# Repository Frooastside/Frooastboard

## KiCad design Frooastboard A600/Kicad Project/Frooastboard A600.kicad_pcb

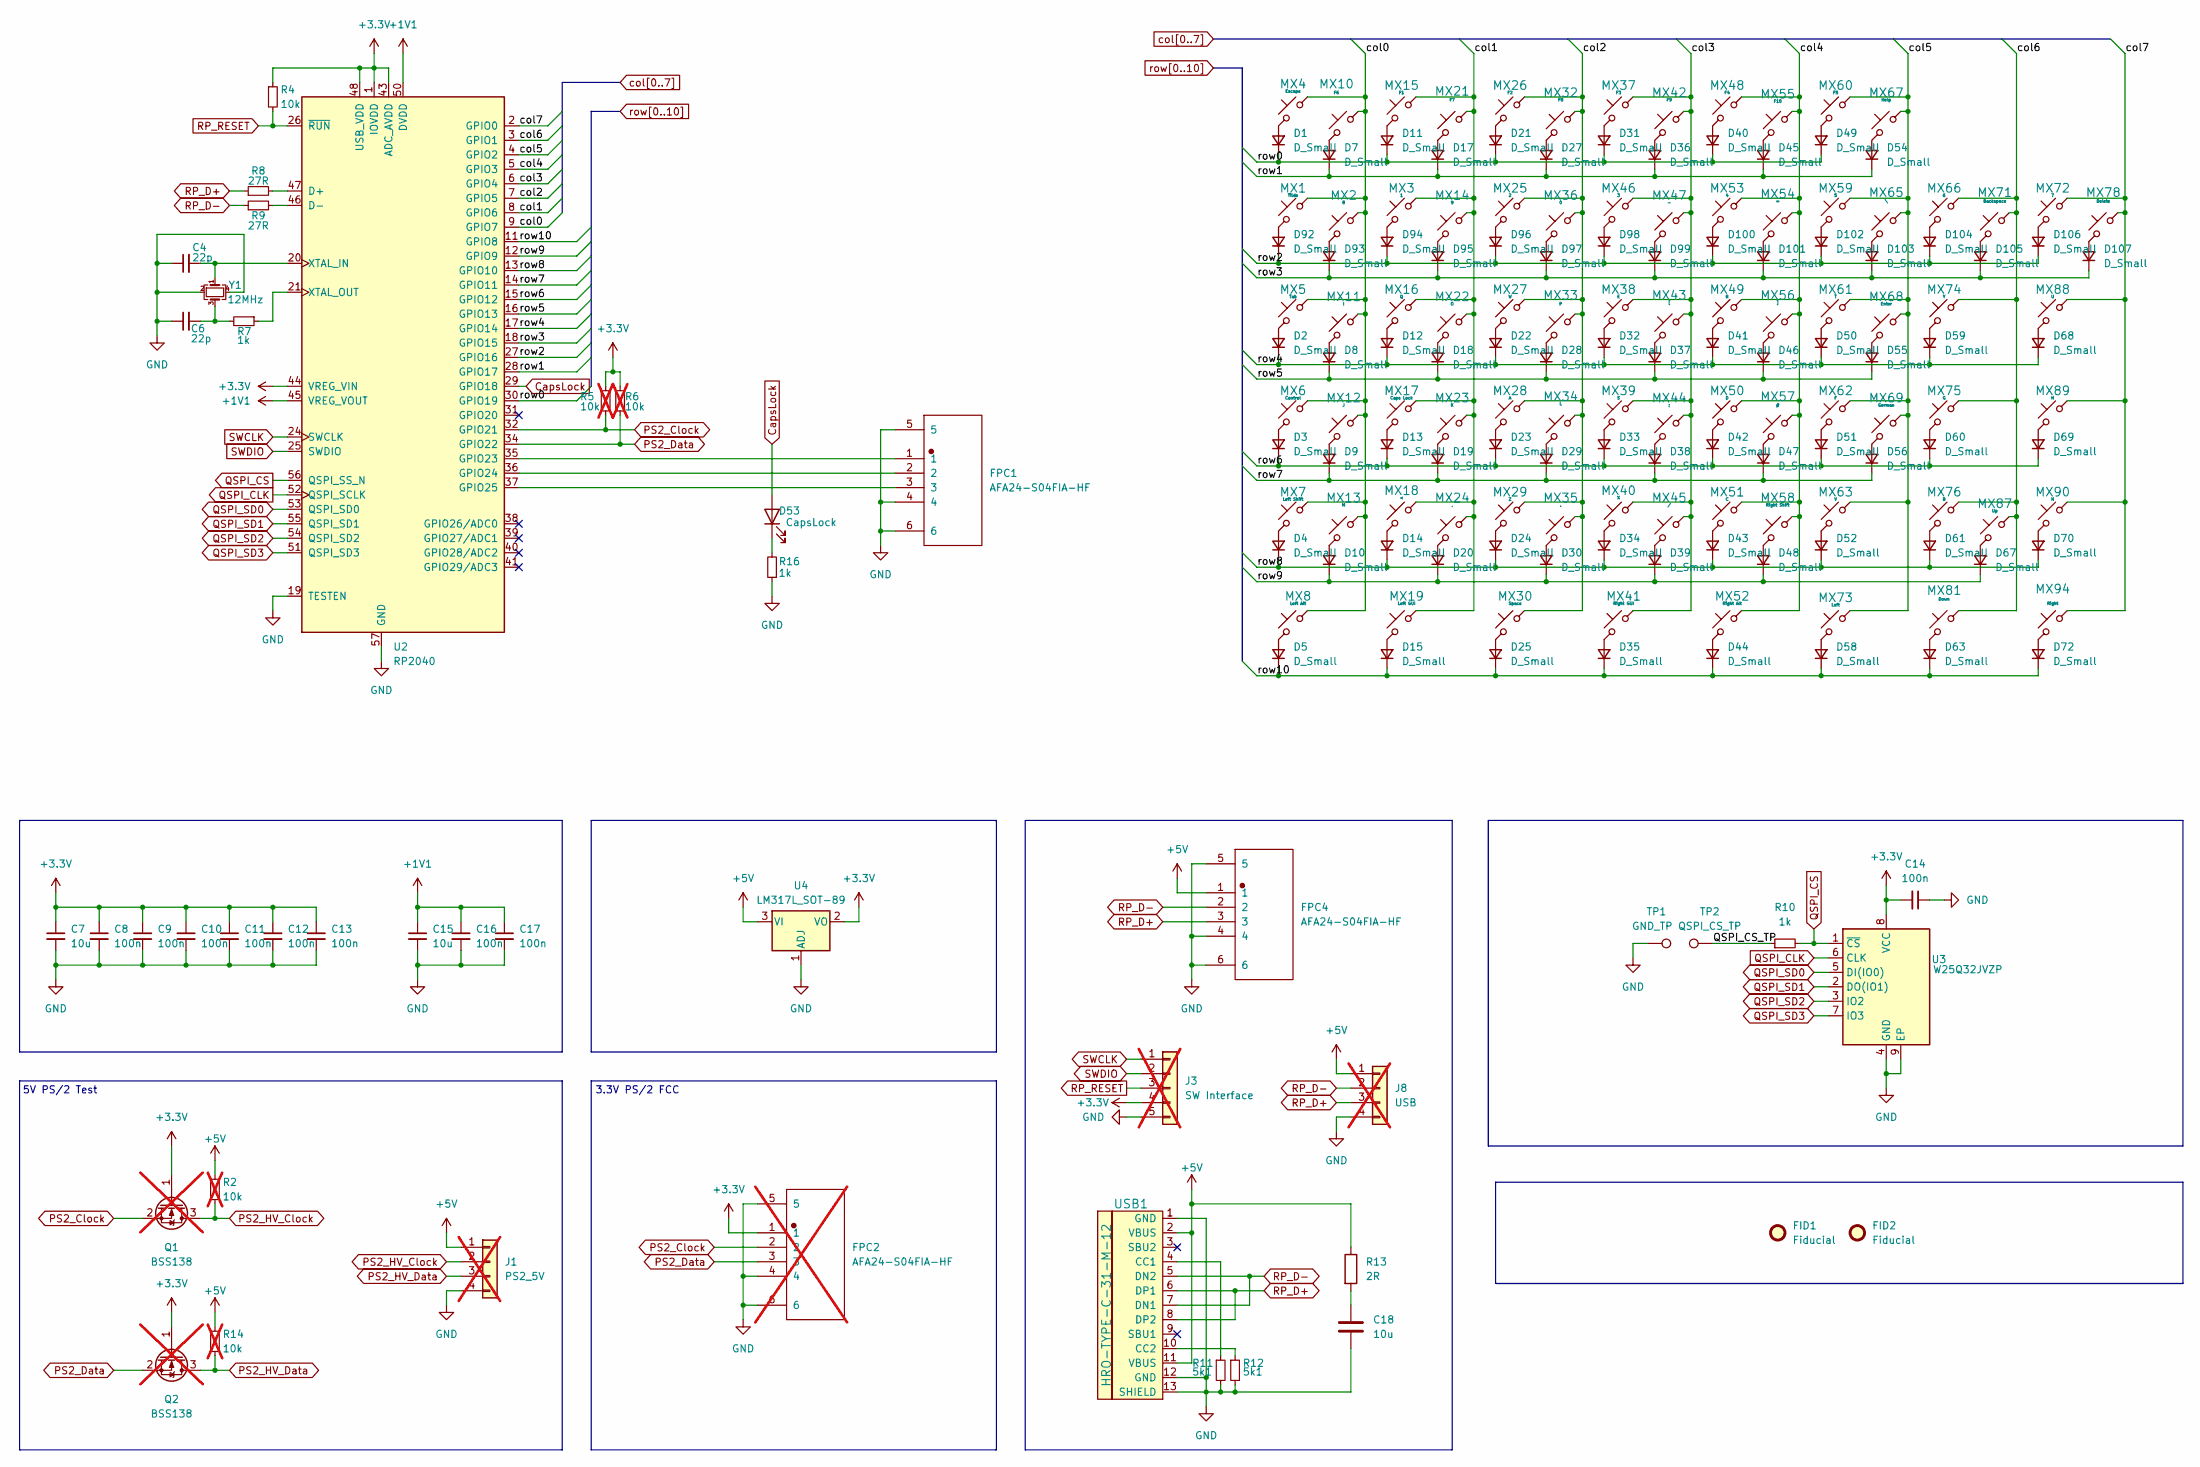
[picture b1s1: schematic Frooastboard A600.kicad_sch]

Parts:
C4, C6: 22p; C_0805_2012Metric
C7, C15, C18: 10u; C_0805_2012Metric
C8, C9, C10, C11, C12, C13, C14, C16, C17: 100n; C_0805_2012Metric
D1, D2, D3, D4, D5, D7, D8, D9, D10, D11, D12, D13, D14, D15, D17, D18, D19, D20, D21, D22, D23, D24, D25, D27, D28, D29, D30, D31, D32, D33, D34, D35, D36, D37, D38, D39, D40, D41, D42, D43, D44, D45, D46, D47, D48, D49, D50, D51, D52, D54, D55, D56, D58, D59, D60, D61, D63, D67, D68, D69, D70, D72, D92, D93, D94, D95, D96, D97, D98, D99, D100, D101, D102, D103, D104, D105, D106, D107: D_Small; D_SOD-323
D53: CapsLock; LED_RGB_SMD_6028_Reverse
FID1, FID2: Fiducial; Fiducial_1mm_Mask2mm
FPC1, FPC4: AFA24-S04FIA-HF; FPC-SMD_4P-P1.00_AFA01-S04FCC-00
FPC2: AFA24-S04FIA-HF; FPC-SMD_4P-P1.00_AFA01-S04FCC-00; not fitted
J1: PS2_5V; PinHeader_1x04_P1.27mm_Vertical; not fitted
J3: SW Interface; PinHeader_1x05_P1.27mm_Vertical; not fitted
J8: USB; PinHeader_1x04_P1.27mm_Vertical; not fitted
MX1: Tilde; MX-Solderable-1.5U
MX2: 8; MX-Solderable-1U
MX3: 1; MX-Solderable-1U
MX4: Escape; MX-Solderable-1.25U
MX5: Tab; MX-Solderable-2U
MX6: Control; MX-Solderable-1.25U
MX7: Left Shift; MX-Solderable-1.75U
MX8: Left Alt; MX-Solderable-1.25U
MX10: F6; MX-Solderable-1.25U
MX11: I; MX-Solderable-1U
MX12: J; MX-Solderable-1U
MX13: M; MX-Solderable-1U
MX14: 9; MX-Solderable-1U
MX15: F1; MX-Solderable-1.25U
MX16: Q; MX-Solderable-1U
MX17: Caps Lock; MX-Solderable-1U
MX18: <; MX-Solderable-1U
MX19: Left GUI; MX-Solderable-1.25U
MX21: F7; MX-Solderable-1.25U
MX22: O; MX-Solderable-1U
MX23: K; MX-Solderable-1U
MX24: ,; MX-Solderable-1U
MX25: 2; MX-Solderable-1U
MX26: F2; MX-Solderable-1.25U
MX27: W; MX-Solderable-1U
MX28: A; MX-Solderable-1U
MX29: Z; MX-Solderable-1U
MX30: Space; MX-Solderable-7U
MX32: F8; MX-Solderable-1.25U
MX33: P; MX-Solderable-1U
MX34: L; MX-Solderable-1U
MX35: .; MX-Solderable-1U
MX36: 0; MX-Solderable-1U
MX37: F3; MX-Solderable-1.25U
MX38: E; MX-Solderable-1U
MX39: S; MX-Solderable-1U
MX40: X; MX-Solderable-1U
MX41: Right GUI; MX-Solderable-1.25U
MX42: F9; MX-Solderable-1.25U
MX43: [; MX-Solderable-1U
MX44: ;; MX-Solderable-1U
MX45: /; MX-Solderable-1U
MX46: 3; MX-Solderable-1U
MX47: -; MX-Solderable-1U
MX48: F4; MX-Solderable-1.25U
MX49: R; MX-Solderable-1U
MX50: D; MX-Solderable-1U
MX51: C; MX-Solderable-1U
MX52: Right Alt; MX-Solderable-1.25U
MX53: 4; MX-Solderable-1U
MX54: =; MX-Solderable-1U
MX55: F10; MX-Solderable-1.25U
MX56: ]; MX-Solderable-1U
MX57: #; MX-Solderable-1U
MX58: Right Shift; MX-Solderable-1.75U
MX59: 5; MX-Solderable-1U
MX60: F5; MX-Solderable-1.25U
MX61: T; MX-Solderable-1U
MX62: F; MX-Solderable-1U
MX63: V; MX-Solderable-1U
MX65: \; MX-Solderable-1U
MX66: 6; MX-Solderable-1U
MX67: Help; MX-Solderable-1.25U
MX68: Enter; MX-Solderable-ISO-Rotated
MX69: German; MX-Solderable-1U
MX71: Backspace; MX-Solderable-1U
MX72: 7; MX-Solderable-1U
MX73: Left; MX-Solderable-1U
MX74: Y; MX-Solderable-1U
MX75: G; MX-Solderable-1U
MX76: B; MX-Solderable-1U
MX78: Delete; MX-Solderable-1U
MX81: Down; MX-Solderable-1U
MX87: Up; MX-Solderable-1U
MX88: U; MX-Solderable-1U
MX89: H; MX-Solderable-1U
MX90: N; MX-Solderable-1U
MX94: Right; MX-Solderable-1U
Q1, Q2: BSS138; SOT-23; not fitted
R2, R5, R6, R14: 10k; R_0805_2012Metric; not fitted
R4: 10k; R_0805_2012Metric
R7, R10, R16: 1k; R_0805_2012Metric
R8, R9: 27R; R_0805_2012Metric
R11, R12: 5k1; R_0805_2012Metric
R13: 2R; R_0805_2012Metric
TP1: GND_TP; TestPoint_Pad_D1.5mm
TP2: QSPI_CS_TP; TestPoint_Pad_D1.5mm
U2: RP2040; RP2040-QFN-56
U3: W25Q32JVZP; WSON-8-1EP_6x5mm_P1.27mm_EP3.4x4.3mm
U4: LM317L_SOT-89; SOT-89-3; LCSC Part # C5120796
USB1: HRO-TYPE-C-31-M-12
Y1: 12MHz; Crystal_SMD_3225-4Pin_3.2x2.5mm

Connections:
+1V1: C15.1, C16.1, C17.1, U2.23 (DVDD), U2.45 (VREG_VOUT), U2.50 (DVDD)
+3.3V: C7.1, C8.1, C9.1, C10.1, C11.1, C12.1, C13.1, C14.2, FPC2.1, J3.4, Q1.1 (G), Q2.1 (G), R4.1, R5.2, R6.2, U2.1 (IOVDD), U2.10 (IOVDD), U2.22 (IOVDD), U2.33 (IOVDD), U2.42 (IOVDD), U2.43 (ADC_AVDD), U2.44 (VREG_VIN), U2.48 (USB_VDD), U2.49 (IOVDD), U3.8 (VCC), U4.2 (VO)
+5V: FPC4.1, J1.1, J8.1, R2.2, R13.1, R14.2, U4.3 (VI), USB1.2 (VBUS), USB1.11 (VBUS)
/QSPI_CS_TP: R10.1, TP2.1
CapsLock: D53.2 (A), U2.29 (GPIO18)
GND: C4.1, C6.1, C7.2, C8.2, C9.2, C10.2, C11.2, C12.2, C13.2, C14.1, C15.2, C16.2, C17.2, C18.2, FPC1.4, FPC1.5, FPC1.6, FPC2.4, FPC2.5, FPC2.6, FPC4.4, FPC4.5, FPC4.6, J1.4, J3.5, J8.4, R11.2, R12.2, R16.1, TP1.1, U2.19 (TESTEN), U2.57 (GND), U3.4 (GND), U3.9 (EP), U4.1 (ADJ), USB1.1 (GND), USB1.12 (GND), USB1.13 (SHIELD), Y1.2, Y1.4
unnamed: C6.2, R7.2, Y1.3
unnamed: C18.1, R13.2
unnamed: D1.2 (A), MX4.2
unnamed: D2.2 (A), MX5.2
unnamed: D3.2 (A), MX6.2
unnamed: D4.2 (A), MX7.2
unnamed: D5.2 (A), MX8.2
unnamed: D7.2 (A), MX10.2
unnamed: D8.2 (A), MX11.2
unnamed: D9.2 (A), MX12.2
unnamed: D10.2 (A), MX13.2
unnamed: D11.2 (A), MX15.2
unnamed: D12.2 (A), MX16.2
unnamed: D13.2 (A), MX17.2
unnamed: D14.2 (A), MX18.2
unnamed: D15.2 (A), MX19.2
unnamed: D17.2 (A), MX21.2
unnamed: D18.2 (A), MX22.2
unnamed: D19.2 (A), MX23.2
unnamed: D20.2 (A), MX24.2
unnamed: D21.2 (A), MX26.2
unnamed: D22.2 (A), MX27.2
unnamed: D23.2 (A), MX28.2
unnamed: D24.2 (A), MX29.2
unnamed: D25.2 (A), MX30.2
unnamed: D27.2 (A), MX32.2
unnamed: D28.2 (A), MX33.2
unnamed: D29.2 (A), MX34.2
unnamed: D30.2 (A), MX35.2
unnamed: D31.2 (A), MX37.2
unnamed: D32.2 (A), MX38.2
unnamed: D33.2 (A), MX39.2
unnamed: D34.2 (A), MX40.2
unnamed: D35.2 (A), MX41.2
unnamed: D36.2 (A), MX42.2
unnamed: D37.2 (A), MX43.2
unnamed: D38.2 (A), MX44.2
unnamed: D39.2 (A), MX45.2
unnamed: D40.2 (A), MX48.2
unnamed: D41.2 (A), MX49.2
unnamed: D42.2 (A), MX50.2
unnamed: D43.2 (A), MX51.2
unnamed: D44.2 (A), MX52.2
unnamed: D45.2 (A), MX55.2
unnamed: D46.2 (A), MX56.2
unnamed: D47.2 (A), MX57.2
unnamed: D48.2 (A), MX58.2
unnamed: D49.2 (A), MX60.2
unnamed: D50.2 (A), MX61.2
unnamed: D51.2 (A), MX62.2
unnamed: D52.2 (A), MX63.2
unnamed: D53.1 (K), R16.2
unnamed: D54.2 (A), MX67.2
unnamed: D55.2 (A), MX68.2
unnamed: D56.2 (A), MX69.2
unnamed: D58.2 (A), MX73.2
unnamed: D59.2 (A), MX74.2
unnamed: D60.2 (A), MX75.2
unnamed: D61.2 (A), MX76.2
unnamed: D63.2 (A), MX81.2
unnamed: D67.2 (A), MX87.2
unnamed: D68.2 (A), MX88.2
unnamed: D69.2 (A), MX89.2
unnamed: D70.2 (A), MX90.2
unnamed: D72.2 (A), MX94.2
unnamed: D92.2 (A), MX1.2
unnamed: D93.2 (A), MX2.2
unnamed: D94.2 (A), MX3.2
unnamed: D95.2 (A), MX14.2
unnamed: D96.2 (A), MX25.2
unnamed: D97.2 (A), MX36.2
unnamed: D98.2 (A), MX46.2
unnamed: D99.2 (A), MX47.2
unnamed: D100.2 (A), MX53.2
unnamed: D101.2 (A), MX54.2
unnamed: D102.2 (A), MX59.2
unnamed: D103.2 (A), MX65.2
unnamed: D104.2 (A), MX66.2
unnamed: D105.2 (A), MX71.2
unnamed: D106.2 (A), MX72.2
unnamed: D107.2 (A), MX78.2
unnamed: R8.2, U2.47 (D+)
unnamed: R9.2, U2.46 (D-)
unnamed: FPC1.1, U2.35 (GPIO23)
unnamed: FPC1.2, U2.36 (GPIO24)
unnamed: FPC1.3, U2.37 (GPIO25)
unnamed: C4.2, U2.20 (XTAL_IN), Y1.1
unnamed: R7.1, U2.21 (XTAL_OUT)
unnamed: R11.1, USB1.4 (CC1)
unnamed: R12.1, USB1.10 (CC2)
PS2_Clock: FPC2.2, Q1.2 (S), R5.1, U2.32 (GPIO21)
PS2_Data: FPC2.3, Q2.2 (S), R6.1, U2.34 (GPIO22)
PS2_HV_Clock: J1.2, Q1.3 (D), R2.1
PS2_HV_Data: J1.3, Q2.3 (D), R14.1
QSPI_CLK: U2.52 (QSPI_SCLK), U3.6 (CLK)
QSPI_CS: R10.2, U2.56 (QSPI_SS_N), U3.1 (~CS)
QSPI_SD0: U2.53 (QSPI_SD0), U3.5 (DI(IO0))
QSPI_SD1: U2.55 (QSPI_SD1), U3.2 (DO(IO1))
QSPI_SD2: U2.54 (QSPI_SD2), U3.3 (IO2)
QSPI_SD3: U2.51 (QSPI_SD3), U3.7 (IO3)
RP_D+: FPC4.3, J8.3, R8.1, USB1.6 (DP1), USB1.8 (DP2)
RP_D-: FPC4.2, J8.2, R9.1, USB1.5 (DN2), USB1.7 (DN1)
RP_RESET: J3.3, R4.2, U2.26 (~RUN)
SWCLK: J3.1, U2.24 (SWCLK)
SWDIO: J3.2, U2.25 (SWDIO)
col0: MX1.1, MX2.1, MX4.1, MX5.1, MX6.1, MX7.1, MX8.1, MX10.1, MX11.1, MX12.1, MX13.1, U2.9 (GPIO7)
col1: MX3.1, MX14.1, MX15.1, MX16.1, MX17.1, MX18.1, MX19.1, MX21.1, MX22.1, MX23.1, MX24.1, U2.8 (GPIO6)
col2: MX25.1, MX26.1, MX27.1, MX28.1, MX29.1, MX30.1, MX32.1, MX33.1, MX34.1, MX35.1, MX36.1, U2.7 (GPIO5)
col3: MX37.1, MX38.1, MX39.1, MX40.1, MX41.1, MX42.1, MX43.1, MX44.1, MX45.1, MX46.1, MX47.1, U2.6 (GPIO4)
col4: MX48.1, MX49.1, MX50.1, MX51.1, MX52.1, MX53.1, MX54.1, MX55.1, MX56.1, MX57.1, MX58.1, U2.5 (GPIO3)
col5: MX59.1, MX60.1, MX61.1, MX62.1, MX63.1, MX65.1, MX67.1, MX68.1, MX69.1, MX73.1, U2.4 (GPIO2)
col6: MX66.1, MX71.1, MX74.1, MX75.1, MX76.1, MX81.1, MX87.1, U2.3 (GPIO1)
col7: MX72.1, MX78.1, MX88.1, MX89.1, MX90.1, MX94.1, U2.2 (GPIO0)
row0: D1.1 (K), D11.1 (K), D21.1 (K), D31.1 (K), D40.1 (K), D49.1 (K), U2.30 (GPIO19)
row1: D7.1 (K), D17.1 (K), D27.1 (K), D36.1 (K), D45.1 (K), D54.1 (K), U2.28 (GPIO17)
row2: D92.1 (K), D94.1 (K), D96.1 (K), D98.1 (K), D100.1 (K), D102.1 (K), D104.1 (K), D106.1 (K), U2.27 (GPIO16)
row3: D93.1 (K), D95.1 (K), D97.1 (K), D99.1 (K), D101.1 (K), D103.1 (K), D105.1 (K), D107.1 (K), U2.18 (GPIO15)
row4: D2.1 (K), D12.1 (K), D22.1 (K), D32.1 (K), D41.1 (K), D50.1 (K), D59.1 (K), D68.1 (K), U2.17 (GPIO14)
row5: D8.1 (K), D18.1 (K), D28.1 (K), D37.1 (K), D46.1 (K), D55.1 (K), U2.16 (GPIO13)
row6: D3.1 (K), D13.1 (K), D23.1 (K), D33.1 (K), D42.1 (K), D51.1 (K), D60.1 (K), D69.1 (K), U2.15 (GPIO12)
row7: D9.1 (K), D19.1 (K), D29.1 (K), D38.1 (K), D47.1 (K), D56.1 (K), U2.14 (GPIO11)
row8: D4.1 (K), D14.1 (K), D24.1 (K), D34.1 (K), D43.1 (K), D52.1 (K), D61.1 (K), D70.1 (K), U2.13 (GPIO10)
row9: D10.1 (K), D20.1 (K), D30.1 (K), D39.1 (K), D48.1 (K), D67.1 (K), U2.12 (GPIO9)
row10: D5.1 (K), D15.1 (K), D25.1 (K), D35.1 (K), D44.1 (K), D58.1 (K), D63.1 (K), D72.1 (K), U2.11 (GPIO8)

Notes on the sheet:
5V PS/2 Test
3.3V PS/2 FCC

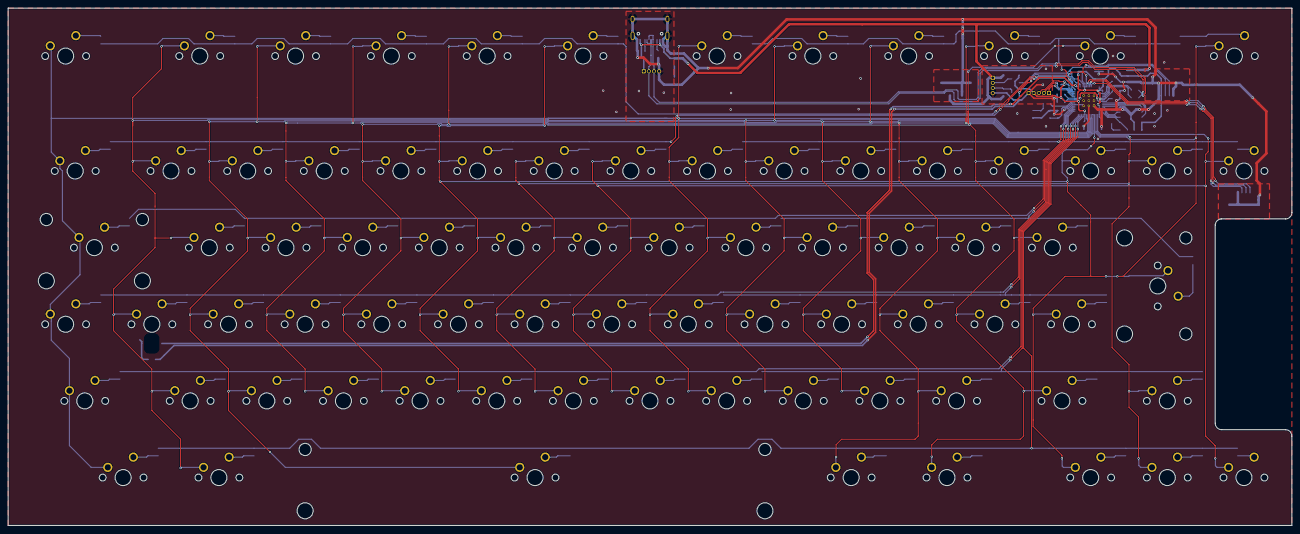
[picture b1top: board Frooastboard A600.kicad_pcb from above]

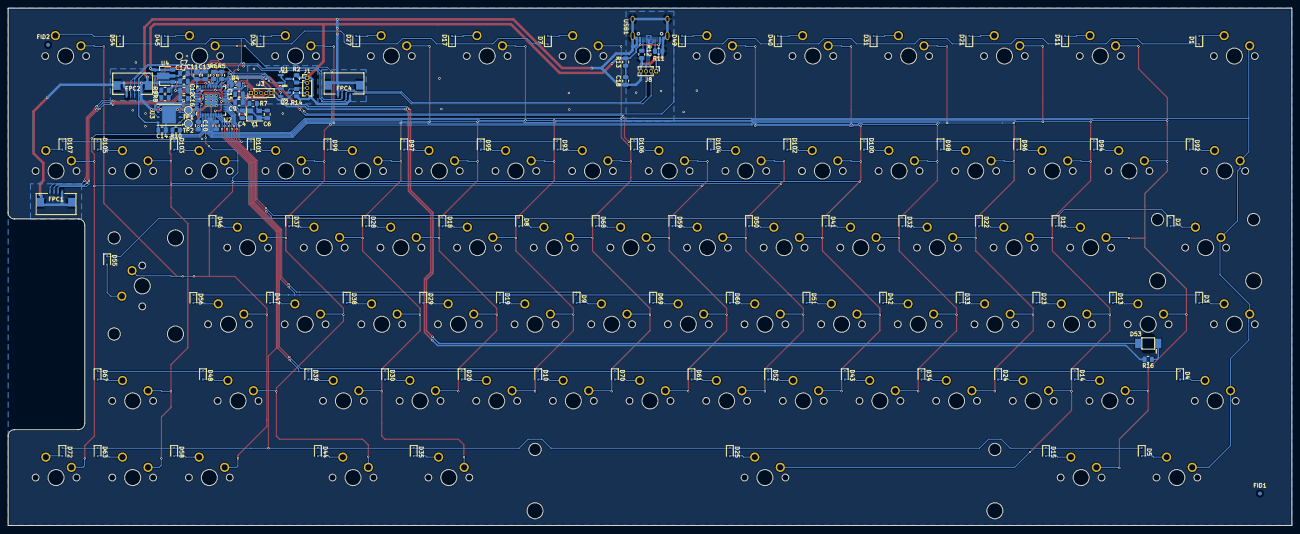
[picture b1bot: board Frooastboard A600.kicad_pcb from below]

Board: 2 copper layers, 319.1 x 128.6 mm, 201 parts (123 on the bottom side), 130 nets.

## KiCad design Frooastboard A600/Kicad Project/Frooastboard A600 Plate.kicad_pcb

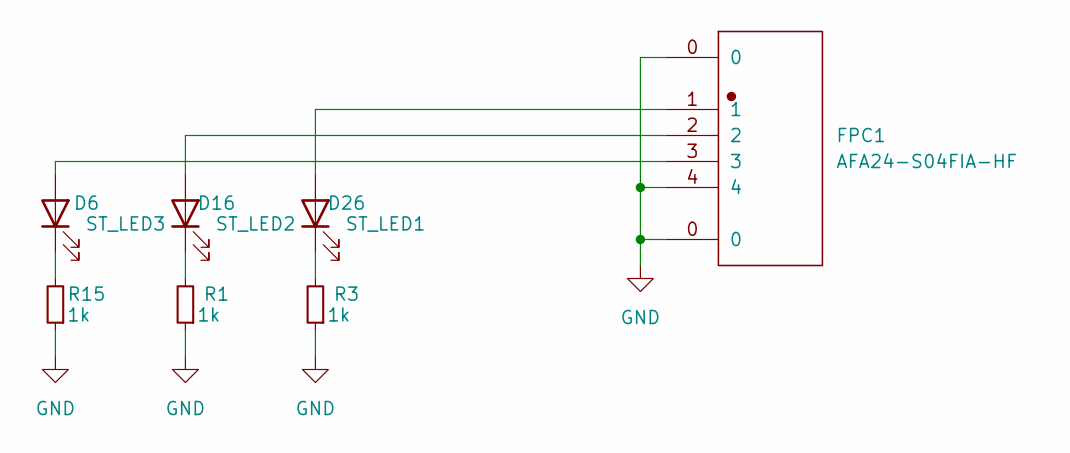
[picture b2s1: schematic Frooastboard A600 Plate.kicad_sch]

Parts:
D6: ST_LED3; LED_RGB_SMD_6028_Reverse
D16: ST_LED2; LED_RGB_SMD_6028_Reverse
D26: ST_LED1; LED_RGB_SMD_6028_Reverse
FPC1: AFA24-S04FIA-HF; FPC-SMD_4P-P1.00_AFA24-S04FIA-HF
R1, R3, R15: 1k; R_0805_2012Metric

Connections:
GND: FPC1.0, FPC1.4, R1.1, R3.1, R15.1
unnamed: D6.2 (A), FPC1.3
unnamed: D6.1 (K), R15.2
unnamed: D16.2 (A), FPC1.2
unnamed: D16.1 (K), R1.2
unnamed: D26.2 (A), FPC1.1
unnamed: D26.1 (K), R3.2

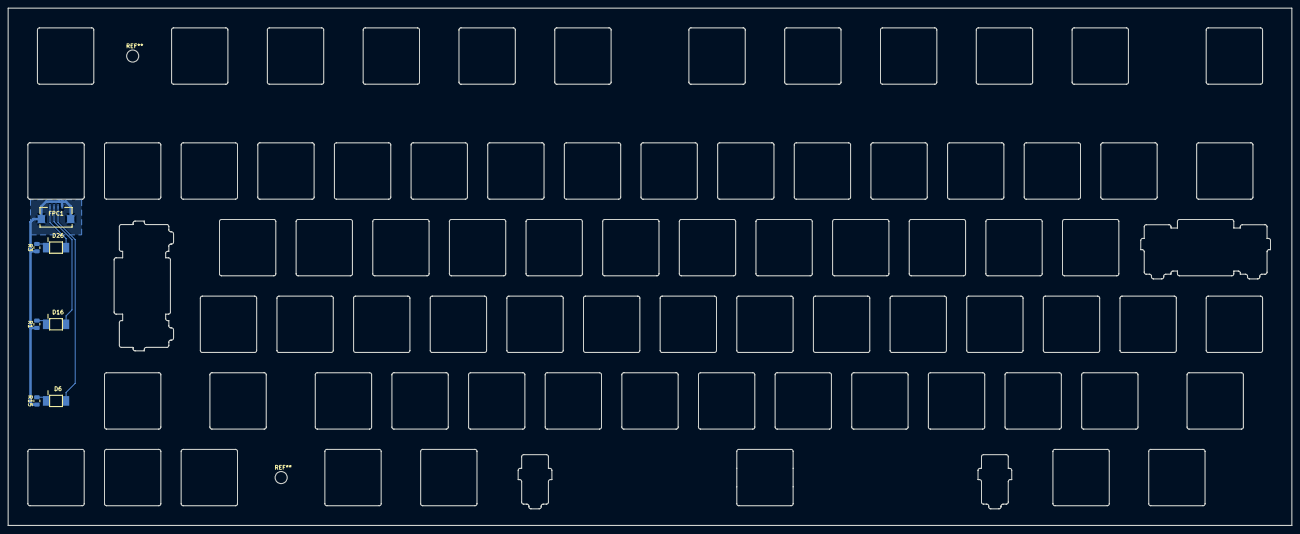
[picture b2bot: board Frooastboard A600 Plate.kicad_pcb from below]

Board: 2 copper layers, 319.1 x 128.6 mm, 7 parts (7 on the bottom side), 7 nets.

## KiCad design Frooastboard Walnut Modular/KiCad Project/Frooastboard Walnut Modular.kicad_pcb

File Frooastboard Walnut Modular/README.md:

#FrooastboardWalnutModular

#LEDs

|     |    |     |    |     |    |     |    |     |    |     |    |     |    |     |    |     |    |     | 10  |     |   |     |   |     |   |     |   |     |   |     |   |     |   |     |   |     |   |     | 20  |     |   |     |     |   |     |   |     |   |     | 25  |     |
|:---:|:---:|:---:|:---:|:---:|:---:|:---:|:---:|:---:|:---:|:---:|:---:|:---:|:---:|:---:|:---:|:---:|:---:|:---:|:---:|:---:|:---:|:---:|:---:|:---:|:---:|:---:|:---:|:---:|:---:|:---:|:---:|:---:|:---:|:---:|:---:|:---:|:---:|:---:|:---:|:---:|:---:|:---:|:---:|:---:|:---:|:---:|:---:|:---:|:---:|:---:|:---:|
|     |  8  | —   |  9  |  —   | 10  | —    | 11  |   —  | 12  |  —   | 13  | —    | 14  |    — | 15  |  —   | 16  |   —  | 17  |    — | X  | —    | 19  |  —   | 20  | —    | 21  |  —   | 22  |   —  | 23  | —    | 24  |  —   | 25  |  —   | 26  |  —   | 27  |   —  | 28  |     |     | 29  |  —   | 30  |  —   | 31  |   —  | 32  |     |
|  7  |     |     |     |     |     |     |     |     |     |     |     |     |     |     |     |     |     |     |     |     |     |     |     |     |     |     |     |     |     |     |     |     |     |     |     |     |     |     |     |     |     | 29   |  28  |     |     |     |     |     |     |     | 33  |
| \|  |  8  |   —  |  9  | —    | 10  | —    | 11  |  —   | 12  |  —   | 13  |   —  | 14  | —    | 15  |  —   | 16  | —    | 17  |   —  | X  |  —   | 19  |  —   | 20  |  —   | 21  |  —   | 22  |  —   | 23  |  —   | 24  |   —  | 25  | —    | 26  |  —   | 27  |  —   | 28  |   \|  | \|    |  29 |   —  |  30 |  — | 31  |  —  | 32  |  \|    |
|  6  |     |     |     |     |     |     |     |     |     |     |     |     |     |     |     |     |     |     |     |     |     |     |     |     |     |     |     |     |     |     |     |     |     |     |     |     |     |     |     |     |     |  34  |  27  |     |     |     |     |     |     |     | 34  |
| \|  |     |     |     |     |     |     |     |     |     |     |     |     |     |     |     |     |     |     |     |     |     |     |     |     |     |     |     |     |     |     |     |     |     |     |     |     |     |     |     |     |     |   \|   |   \|   |     |     |     |     |     |     |     |  \|    |
|  5  |     |     |     |     |     |     |     |     |     |     |     |     |     |     |     |     |     |     |     |     |     |     |     |     |     |     |     |     |     |     |     |     |     |     |     |     |     |     |     |     |     |  35   |  26  |     |     |     |     |     |     |     | 35  |
| \|  |     |     |     |     |     |     |     |     |     |     |     |     |     |     |     |     |     |     |     |     |     |     |     |     |     |     |     |     |     |     |     |     |     |     |     |     |     |     |     |     |     |   \|   |   \|   |     |     |     |     |     |     |     | \|     |
|  4  |     |     |     |     |     |     |     |     |     |     |     |     |     |     |     |     |     |     |     |     |     |     |     |     |     |     |     |     |     |     |     |     |     |     |     |     |     |     |     |     |     | 36   |  25   |     |     |     |     |     |     |     | 36  |
| \|  |     |     |     |     |     |     |     |     |     |     |     |     |     |     |     |     |     |     |     |     |     |     |     |     |     |     |     |     |     |     |     |     |     |     |     |     |     |     |     |     |     |   \|   |   \|   |     |     |     |     |     |     |     |  \|    |
|  3  |     |     |     |     |     |     |     |     |     |     |     |     |     |     |     |     |     |     |     |     |     |     |     |     |     |     |     |     |     |     |     |     |     |     |     |     |     |     |     |     |     |   37  | 24    |     |     |     |     |     |     |     | 37  |
| \|  |     |     |     |     |     |     |     |     |     |     |     |     |     |     |     |     |     |     |     |     |     |     |     |     |     |     |     |     |     |     |     |     |     |     |     |     |     |     |     |     |     |   \|   |   \|   |     |     |     |     |     |     |     |  \|    |
|  2  |     |     |     |     |     |     |     |     |     |     |     |     |     |     |     |     |     |     |     |     |     |     |     |     |     |     |     |     |     |     |     |     |     |     |     |     |     |     |     |     |     | 38    |   23  |     |     |     |     |     |     |     | 38  |
| \|  |     |     |     |     |     |     |     |     |     |     |     |     |     |     |     |     |     |     |     |     |     |     |     |     |     |     |     |     |     |     |     |     |     |     |     |     |     |     |     |     |     |   \|   |  \|    |     |     |     |     |     |     |     | \|     |
|  1  |     |     |     |     |     |     |     |     |     |     |     |     |     |     |     |     |     |     |     |     |     |     |     |     |     |     |     |     |     |     |     |     |     |     |     |     |     |     |     |     |     |  39  |  22  |     |     |     |     |     |     |     | 39  |
|     | 64  |  —  | 63  |  —  | 62  |  —  | 61  |  —  | 60  |  —  | 59  |  —  | 58  |  —  | 57  |  —  | 56  |  —  | 55  |  —  | 54  |  —  | 53  |  —  | 52  |  —  | 51  |  —  | 50  |  —  | 49  |  —  | 48  |  —  | 47  |  —  | 46  |  —  | 45  |  —  | 44  |  —  | —  | 43  |  —  |  42  |  —  |  41  |  —  |  40  |     |     |
|     |     |     |     |     |     |     |     |     |     |     |     |     |     |     |     |     |     |     |     |     |     |     |     |     |     |     |     |     |     |     |     |     |     |     |     |     |     |     |     |     |     |     |     |     |     |     |     |     |     |     |     |

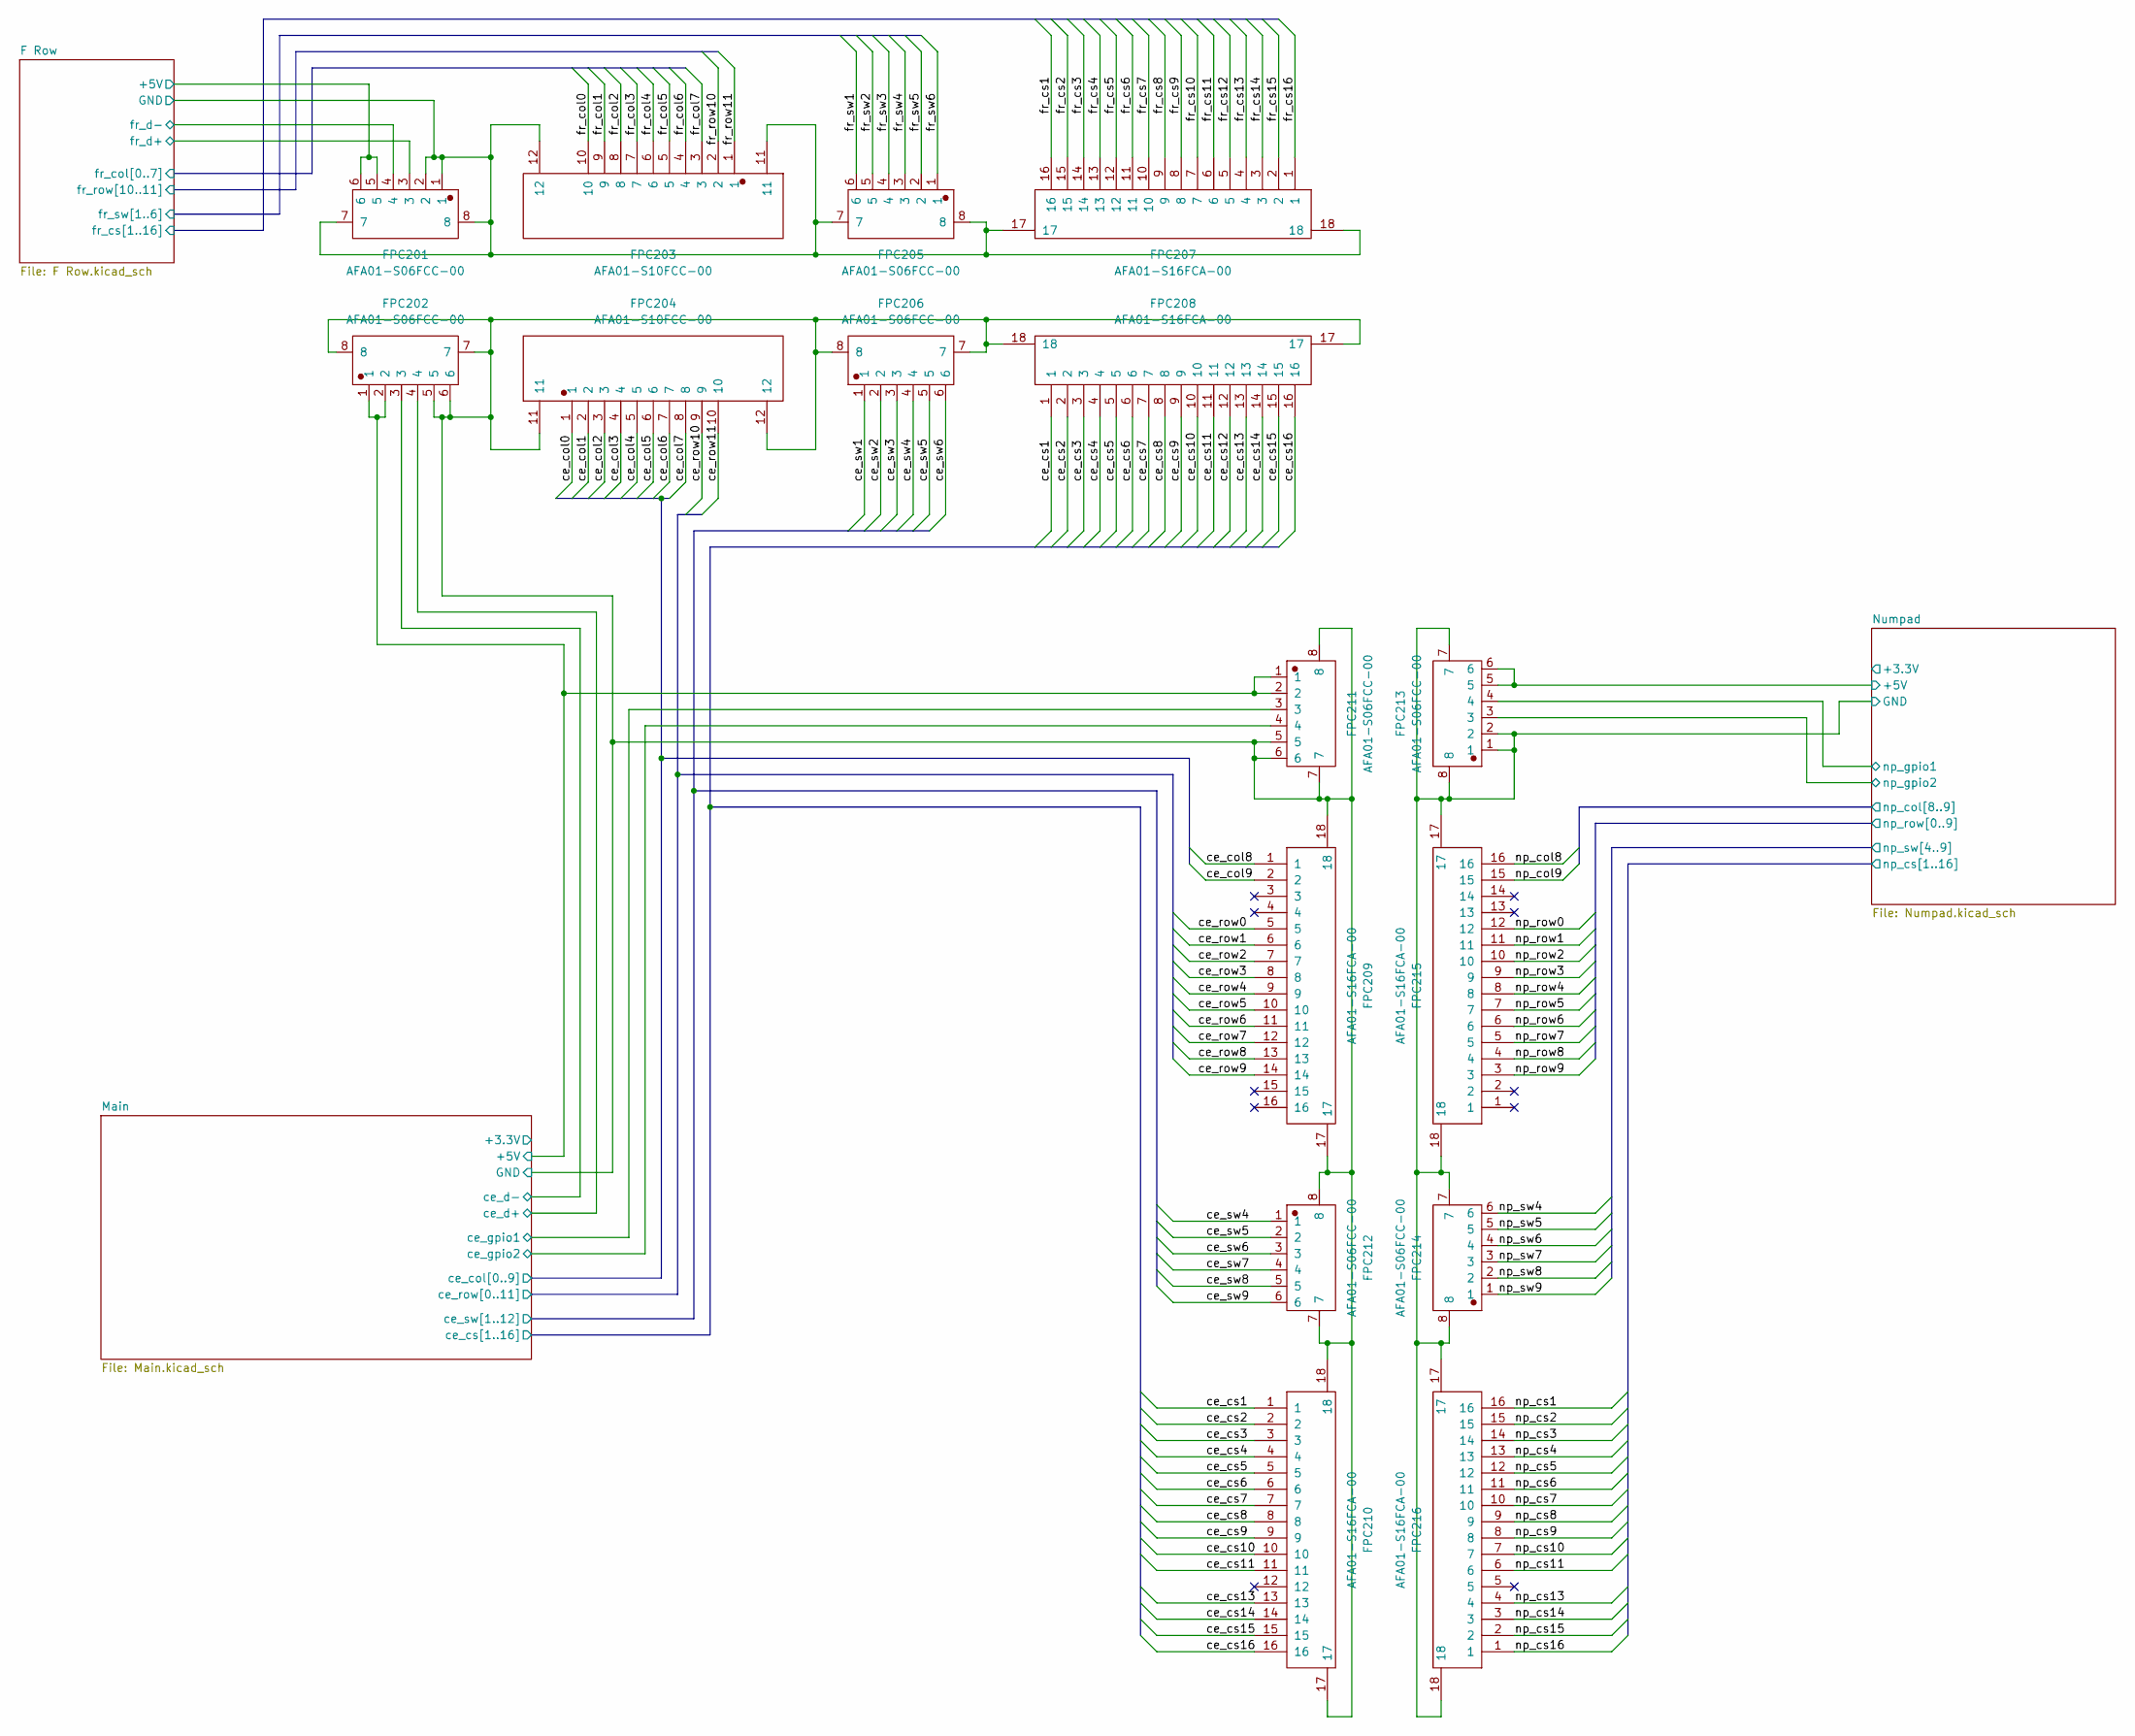
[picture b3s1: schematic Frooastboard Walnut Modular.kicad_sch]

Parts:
FPC201, FPC202, FPC205, FPC206, FPC211, FPC212, FPC213, FPC214: AFA01-S06FCC-00; FPC-SMD_6P-P1.00_AFA01-S06FCC-00
FPC203, FPC204: AFA01-S10FCC-00; FPC-SMD_10P-P1.00_AFA01-S10FCC-00
FPC207, FPC208, FPC209, FPC210, FPC215, FPC216: AFA01-S16FCA-00; FPC-SMD_16P-P1.00_AFA01-S16FCC-00

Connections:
/F Row/+5V: FPC201.5, FPC201.6; also elsewhere on the board
/F Row/GND: FPC201.1, FPC201.2, FPC201.7, FPC201.8, FPC203.11, FPC203.12, FPC205.7, FPC205.8, FPC207.17, FPC207.18; also elsewhere on the board
/F Row/fr_col0: FPC203.10; also elsewhere on the board
/F Row/fr_col1: FPC203.9; also elsewhere on the board
/F Row/fr_col2: FPC203.8; also elsewhere on the board
/F Row/fr_col3: FPC203.7; also elsewhere on the board
/F Row/fr_col4: FPC203.6; also elsewhere on the board
/F Row/fr_col5: FPC203.5; also elsewhere on the board
/F Row/fr_col6: FPC203.4; also elsewhere on the board
/F Row/fr_col7: FPC203.3; also elsewhere on the board
/F Row/fr_cs1: FPC207.16; also elsewhere on the board
/F Row/fr_cs2: FPC207.15
/F Row/fr_cs3: FPC207.14; also elsewhere on the board
/F Row/fr_cs4: FPC207.13; also elsewhere on the board
/F Row/fr_cs5: FPC207.12; also elsewhere on the board
/F Row/fr_cs6: FPC207.11; also elsewhere on the board
/F Row/fr_cs7: FPC207.10; also elsewhere on the board
/F Row/fr_cs8: FPC207.9; also elsewhere on the board
/F Row/fr_cs9: FPC207.8; also elsewhere on the board
/F Row/fr_cs10: FPC207.7; also elsewhere on the board
/F Row/fr_cs11: FPC207.6; also elsewhere on the board
/F Row/fr_cs12: FPC207.5; also elsewhere on the board
/F Row/fr_cs13: FPC207.4; also elsewhere on the board
/F Row/fr_cs14: FPC207.3; also elsewhere on the board
/F Row/fr_cs15: FPC207.2; also elsewhere on the board
/F Row/fr_cs16: FPC207.1; also elsewhere on the board
/F Row/fr_d+: FPC201.3; also elsewhere on the board
/F Row/fr_d-: FPC201.4; also elsewhere on the board
/F Row/fr_row10: FPC203.2; also elsewhere on the board
/F Row/fr_row11: FPC203.1; also elsewhere on the board
/F Row/fr_sw1: FPC205.6; also elsewhere on the board
/F Row/fr_sw2: FPC205.5; also elsewhere on the board
/F Row/fr_sw3: FPC205.4; also elsewhere on the board
/Main/+5V: FPC202.1, FPC202.2, FPC211.1, FPC211.2; also elsewhere on the board
/Main/GND: FPC202.5, FPC202.6, FPC202.7, FPC202.8, FPC204.11, FPC204.12, FPC206.7, FPC206.8, FPC208.17, FPC208.18, FPC209.17, FPC209.18, FPC210.17, FPC210.18, FPC211.5, FPC211.6, FPC211.7, FPC211.8, FPC212.7, FPC212.8; also elsewhere on the board
/Main/ce_col0: FPC204.1; also elsewhere on the board
/Main/ce_col1: FPC204.2; also elsewhere on the board
/Main/ce_col2: FPC204.3; also elsewhere on the board
/Main/ce_col3: FPC204.4; also elsewhere on the board
/Main/ce_col4: FPC204.5; also elsewhere on the board
/Main/ce_col5: FPC204.6; also elsewhere on the board
/Main/ce_col6: FPC204.7; also elsewhere on the board
/Main/ce_col7: FPC204.8; also elsewhere on the board
/Main/ce_col8: FPC209.1; also elsewhere on the board
/Main/ce_col9: FPC209.2; also elsewhere on the board
/Main/ce_cs1: FPC208.1, FPC210.1; also elsewhere on the board
/Main/ce_cs2: FPC208.2, FPC210.2; also elsewhere on the board
/Main/ce_cs3: FPC208.3, FPC210.3; also elsewhere on the board
/Main/ce_cs4: FPC208.4, FPC210.4; also elsewhere on the board
/Main/ce_cs5: FPC208.5, FPC210.5; also elsewhere on the board
/Main/ce_cs6: FPC208.6, FPC210.6; also elsewhere on the board
/Main/ce_cs7: FPC208.7, FPC210.7; also elsewhere on the board
/Main/ce_cs8: FPC208.8, FPC210.8; also elsewhere on the board
/Main/ce_cs9: FPC208.9, FPC210.9; also elsewhere on the board
/Main/ce_cs10: FPC208.10, FPC210.10; also elsewhere on the board
/Main/ce_cs11: FPC208.11, FPC210.11; also elsewhere on the board
/Main/ce_cs12: FPC208.12; also elsewhere on the board
/Main/ce_cs13: FPC208.13, FPC210.13; also elsewhere on the board
/Main/ce_cs14: FPC208.14, FPC210.14; also elsewhere on the board
/Main/ce_cs15: FPC208.15, FPC210.15; also elsewhere on the board
/Main/ce_cs16: FPC208.16, FPC210.16; also elsewhere on the board
/Main/ce_d+: FPC202.4; also elsewhere on the board
/Main/ce_d-: FPC202.3; also elsewhere on the board
/Main/ce_gpio1: FPC211.3; also elsewhere on the board
/Main/ce_gpio2: FPC211.4; also elsewhere on the board
/Main/ce_row0: FPC209.5; also elsewhere on the board
/Main/ce_row1: FPC209.6; also elsewhere on the board
/Main/ce_row2: FPC209.7; also elsewhere on the board
/Main/ce_row3: FPC209.8; also elsewhere on the board
/Main/ce_row4: FPC209.9; also elsewhere on the board
/Main/ce_row5: FPC209.10; also elsewhere on the board
/Main/ce_row6: FPC209.11; also elsewhere on the board
/Main/ce_row7: FPC209.12; also elsewhere on the board
/Main/ce_row8: FPC209.13; also elsewhere on the board
/Main/ce_row9: FPC209.14; also elsewhere on the board
/Main/ce_row10: FPC204.9; also elsewhere on the board
/Main/ce_row11: FPC204.10; also elsewhere on the board
/Main/ce_sw1: FPC206.1; also elsewhere on the board
/Main/ce_sw2: FPC206.2; also elsewhere on the board
/Main/ce_sw3: FPC206.3; also elsewhere on the board
/Main/ce_sw4: FPC206.4, FPC212.1; also elsewhere on the board
/Main/ce_sw5: FPC206.5, FPC212.2; also elsewhere on the board
/Main/ce_sw6: FPC206.6, FPC212.3; also elsewhere on the board
/Numpad/+5V: FPC213.5, FPC213.6; also elsewhere on the board
/Numpad/GND: FPC213.1, FPC213.2, FPC213.7, FPC213.8, FPC214.7, FPC214.8, FPC215.17, FPC215.18, FPC216.17, FPC216.18; also elsewhere on the board
/Numpad/np_col8: FPC215.16; also elsewhere on the board
/Numpad/np_col9: FPC215.15; also elsewhere on the board
/Numpad/np_cs1: FPC216.16; also elsewhere on the board
/Numpad/np_cs2: FPC216.15; also elsewhere on the board
/Numpad/np_cs3: FPC216.14; also elsewhere on the board
/Numpad/np_cs4: FPC216.13; also elsewhere on the board
/Numpad/np_cs5: FPC216.12; also elsewhere on the board
/Numpad/np_cs6: FPC216.11; also elsewhere on the board
/Numpad/np_cs7: FPC216.10; also elsewhere on the board
/Numpad/np_cs8: FPC216.9; also elsewhere on the board
/Numpad/np_cs9: FPC216.8; also elsewhere on the board
/Numpad/np_cs10: FPC216.7; also elsewhere on the board
/Numpad/np_cs11: FPC216.6; also elsewhere on the board
/Numpad/np_cs13: FPC216.4; also elsewhere on the board
/Numpad/np_cs14: FPC216.3; also elsewhere on the board
/Numpad/np_cs15: FPC216.2; also elsewhere on the board
/Numpad/np_cs16: FPC216.1; also elsewhere on the board
/Numpad/np_gpio1: FPC213.4; also elsewhere on the board
/Numpad/np_gpio2: FPC213.3; also elsewhere on the board
/Numpad/np_row0: FPC215.12; also elsewhere on the board
/Numpad/np_row1: FPC215.11; also elsewhere on the board
/Numpad/np_row2: FPC215.10; also elsewhere on the board
/Numpad/np_row3: FPC215.9; also elsewhere on the board
/Numpad/np_row4: FPC215.8; also elsewhere on the board
/Numpad/np_row5: FPC215.7; also elsewhere on the board
/Numpad/np_row6: FPC215.6; also elsewhere on the board
/Numpad/np_row7: FPC215.5; also elsewhere on the board
/Numpad/np_row8: FPC215.4; also elsewhere on the board
/Numpad/np_row9: FPC215.3; also elsewhere on the board
/Numpad/np_sw4: FPC214.6; also elsewhere on the board
/Numpad/np_sw5: FPC214.5; also elsewhere on the board
/Numpad/np_sw6: FPC214.4; also elsewhere on the board
/Numpad/np_sw7: FPC214.3; also elsewhere on the board
/Numpad/np_sw8: FPC214.2; also elsewhere on the board
/Numpad/np_sw9: FPC214.1; also elsewhere on the board
